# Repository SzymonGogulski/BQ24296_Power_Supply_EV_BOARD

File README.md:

# BQ24296 Power Supply 5V @ 3A

### Linki
* [Simple way to use USB-C 5V@3A](https://forum.digikey.com/t/simple-way-to-use-usb-type-c-to-get-5v-at-up-to-3a-15w/7016)

### Notatki
* BQ24296
    * Sprawdź default input current limit,
    * Sprawdź czy wyjście VSYS jest regulowane na 5.0V,
    * Sprawdź co to NVDC power path management,

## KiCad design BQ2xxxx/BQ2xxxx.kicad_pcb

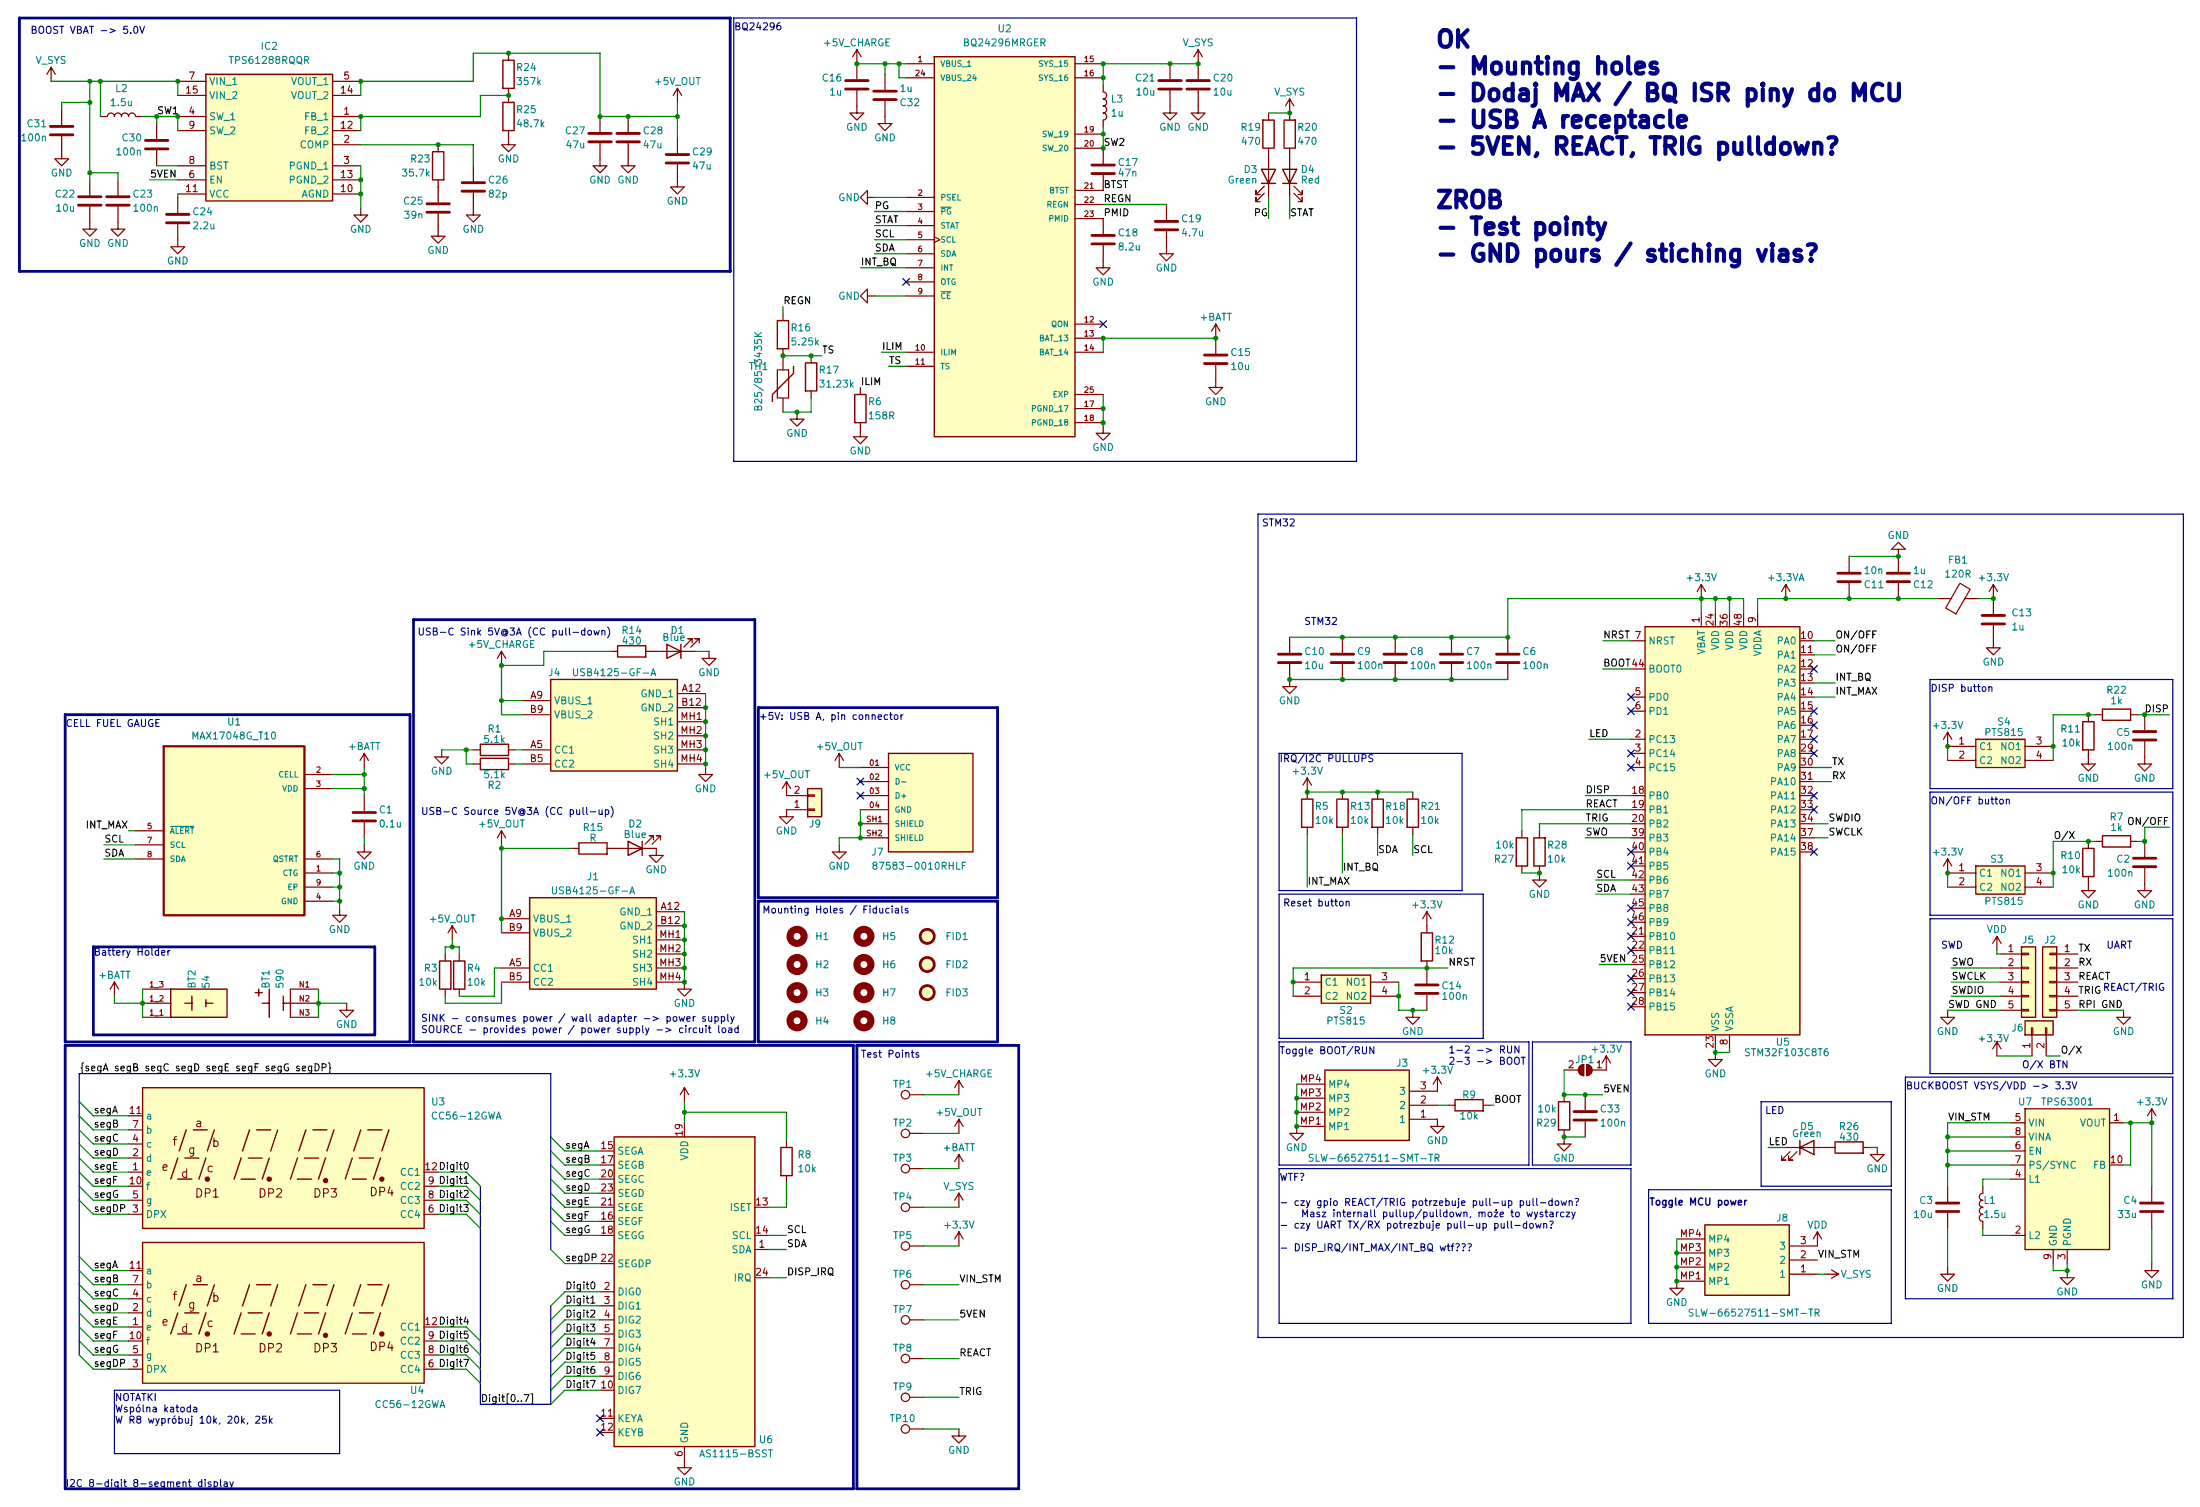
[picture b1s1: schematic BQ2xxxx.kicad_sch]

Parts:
BT1: 590; BAT_590; PARTREV E
BT2: 54; BAT_54; PARTREV E
C1: 0.1u; C_0402_1005Metric
C2, C5, C6, C7, C8, C9, C14, C23, C30, C31, C33: 100n; C_0402_1005Metric
C3, C10, C15, C20, C21: 10u; C_0603_1608Metric
C4: 33u; C_0805_2012Metric
C11: 10n; C_0402_1005Metric
C12, C13, C16, C32: 1u; C_0402_1005Metric
C17: 47n; C_0402_1005Metric
C18: 8.2u; C_0603_1608Metric
C19: 4.7u; C_0603_1608Metric
C22: 10u; C_0805_2012Metric
C24: 2.2u; C_0402_1005Metric
C25: 39n; C_0402_1005Metric
C26: 82p; C_0402_1005Metric
C27, C28, C29: 47u; C_0805_2012Metric
D1, D2: Blue; LED_0402_1005Metric
D3, D5: Green; LED_0402_1005Metric
D4: Red; LED_0402_1005Metric
FB1: 120R; R_0402_1005Metric
FID1, FID2, FID3: Fiducial; stencil_pin
H1, H2, H3, H4, H5, H6, H7, H8: MountingHole; MountingHole_2.2mm_M2
IC2: TPS61288RQQR; Mouser Part Number 595-TPS61288RQQR
J1, J4: USB4125-GF-A; USB4125GFA; Manufacturer_Part_Number USB4125-GF-A
J2, J5: Conn_01x05; PinSocket_1x05_P2.54mm_Vertical
J3, J8: SLW-66527511-SMT-TR; SLW66527511SMTTR; Mouser Part Number 179-SLW66527511SMTTR
J6, J9: Conn_01x02; PinHeader_1x02_P2.54mm_Vertical
J7: 87583-0010RHLF; AMPHENOL_87583-0010RHLF; PARTREV AD
JP1: SolderJumper_2_Open; R_0805_2012Metric
L1: 1.5u; L_1008_2520Metric
L2: 1.5u; L_6.3x6.3_H3
L3: 1u; IND_R2M01_VIS
R1, R2: 5.1k; R_0402_1005Metric
R3, R4, R5, R8, R9, R10, R11, R12, R13, R18, R21, R27, R28, R29: 10k; R_0402_1005Metric
R6: 158R; R_0402_1005Metric
R7, R22: 1k; R_0402_1005Metric
R14, R26: 430; R_0402_1005Metric
R15: R; R_0402_1005Metric
R16: 5.25k; R_0402_1005Metric
R17: 31.23k; R_0402_1005Metric
R19, R20: 470; R_0402_1005Metric
R23: 35.7k; R_0402_1005Metric
R24: 357k; R_0402_1005Metric
R25: 48.7k; R_0402_1005Metric
S2, S3, S4: PTS815; PTS815SJM250SMTRLFS; Mouser Part Number 611-PTS815SJM250SMTR
TH1: B25/85 3435K; R_0805_2012Metric
TP1, TP2, TP3, TP4, TP5, TP6, TP7, TP8, TP9: TestPoint; TestPoint_Pad_1.0x1.0mm
TP10: TestPoint; TestPoint_Pad_D3.0mm
U1: MAX17048G_T10; SON50P200X200X80-9N; DigiKey_Part_Number MAX17048G+T10TR-ND
U2: BQ24296MRGER; QFN50P400X400X100-25N; PARTREV 4219013/A 05/2017
U3, U4: CC56-12GWA
U5: STM32F103C8T6; LQFP-48_7x7mm_P0.5mm
U6: AS1115-BSST; QSOP-24_3.9x8.7mm_P0.635mm
U7: TPS63001; Texas_DRC0010J

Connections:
+3.3V: C4.1, C6.1, C7.1, C8.1, C9.1, C10.1, C13.1, FB1.2, J3.3, J6.1, JP1.1 (A), R5.1, R8.1, R12.1, R13.1, R18.1, R21.1, S3.1 (C1), S3.2 (C2), S4.1 (C1), S4.2 (C2), TP5.1, U5.1 (VBAT), U5.24 (VDD), U5.36 (VDD), U5.48 (VDD), U6.19 (VDD), U7.1 (VOUT), U7.10 (FB)
+3.3VA: C11.1, C12.1, FB1.1, U5.9 (VDDA)
+5V_CHARGE: C16.1, C32.2, J4.A9 (VBUS_1), J4.B9 (VBUS_2), R14.1, TP1.1, U2.1 (VBUS_1), U2.24 (VBUS_24)
+5V_OUT: C27.1, C28.1, C29.1, IC2.5 (VOUT_1), IC2.14 (VOUT_2), J1.A9 (VBUS_1), J1.B9 (VBUS_2), J7.01 (VCC), J9.2, R3.1, R4.1, R15.1, R24.1, TP2.1
+BATT: BT2.1_1, BT2.1_2, BT2.1_3, C1.1, C15.1, TP3.1, U1.2 (CELL), U1.3 (VDD), U2.13 (BAT_13), U2.14 (BAT_14)
/5VEN: C33.1, IC2.6 (EN), JP1.2 (B), R29.1, TP7.1, U5.25 (PB12)
/BOOT: R9.2, U5.44 (BOOT0)
/BTST: C17.2, U2.21 (BTST)
/DISP: C5.1, R22.2, U5.18 (PB0)
/DISP_IRQ: U6.24 (IRQ)
/Digit0: U3.12 (CC1), U6.2 (DIG0)
/Digit1: U3.9 (CC2), U6.3 (DIG1)
/Digit2: U3.8 (CC3), U6.4 (DIG2)
/Digit3: U3.6 (CC4), U6.5 (DIG3)
/Digit4: U4.12 (CC1), U6.7 (DIG4)
/Digit5: U4.9 (CC2), U6.8 (DIG5)
/Digit6: U4.8 (CC3), U6.9 (DIG6)
/Digit7: U4.6 (CC4), U6.10 (DIG7)
/ILIM: R6.1, U2.10 (ILIM)
/INT_BQ: R13.2, U2.7 (INT), U5.13 (PA3)
/INT_MAX: R5.2, U1.5 (~ALERT), U5.14 (PA4)
/LED: D5.1 (K), U5.2 (PC13)
/NRST: C14.1, R12.2, S2.1 (C1), S2.2 (C2), U5.7 (NRST)
/ON/OFF: C2.1, R7.2, U5.10 (PA0), U5.11 (PA1)
/O/X: J6.2, R7.1, R10.1, S3.3 (NO1), S3.4 (NO2)
/PG: D3.1 (K), U2.3 (~PG)
/PMID: C18.1, U2.23 (PMID)
/REACT: J2.3, R27.1, TP8.1, U5.19 (PB1)
/REGN: C19.1, R16.1, U2.22 (REGN)
/RX: J2.2, U5.31 (PA10)
/SCL: R21.2, U1.7 (SCL), U2.5 (SCL), U5.42 (PB6), U6.14 (SCL)
/SDA: R18.2, U1.8 (SDA), U2.6 (SDA), U5.43 (PB7), U6.1 (SDA)
/STAT: D4.1 (K), U2.4 (STAT)
/SW1: C30.2, IC2.4 (SW_1), IC2.9 (SW_2), L2.1
/SW2: C17.1, L3.2, U2.19 (SW_19), U2.20 (SW_20)
/SWCLK: J5.3, U5.37 (PA14)
/SWDIO: J5.4, U5.34 (PA13)
/SWO: J5.2, U5.39 (PB3)
/TRIG: J2.4, R28.2, TP9.1, U5.20 (PB2)
/TS: R16.2, R17.1, TH1.1, U2.11 (TS)
/TX: J2.1, U5.30 (PA9)
/VIN_STM: C3.1, J8.2, TP6.1, U7.5 (VIN), U7.6 (EN), U7.7 (PS/SYNC), U7.8 (VINA)
/segA: U3.11 (a), U4.11 (a), U6.15 (SEGA)
/segB: U3.7 (b), U4.7 (b), U6.17 (SEGB)
/segC: U3.4 (c), U4.4 (c), U6.20 (SEGC)
/segD: U3.2 (d), U4.2 (d), U6.23 (SEGD)
/segDP: U3.3 (DPX), U4.3 (DPX), U6.22 (SEGDP)
/segE: U3.1 (e), U4.1 (e), U6.21 (SEGE)
/segF: U3.10 (f), U4.10 (f), U6.16 (SEGF)
/segG: U3.5 (g), U4.5 (g), U6.18 (SEGG)
GND: BT1.N1, BT1.N2, BT1.N3, C1.2, C2.2, C3.2, C4.2, C5.2, C6.2, C7.2, C8.2, C9.2, C10.2, C11.2, C12.2, C13.2, C14.2, C15.2, C16.2, C18.2, C19.2, C20.2, C21.2, C22.1, C23.2, C24.2, C25.2, C26.2, C27.2, C28.2, C29.2, C31.2, C32.1, C33.2, D1.1 (K), D2.1 (K), IC2.3 (PGND_1), IC2.10 (AGND), IC2.13 (PGND_2), J1.A12 (GND_1), J1.B12 (GND_2), J1.MH1 (SH1), J1.MH2 (SH2), J1.MH3 (SH3), J1.MH4 (SH4), J2.5, J3.1, J3.MP1, J3.MP2, J3.MP3, J3.MP4, J4.A12 (GND_1), J4.B12 (GND_2), J4.MH1 (SH1), J4.MH2 (SH2), J4.MH3 (SH3), J4.MH4 (SH4), J5.5, J7.04 (GND), J7.SH1 (SHIELD), J7.SH2 (SHIELD), J8.MP1, J8.MP2, J8.MP3, J8.MP4, J9.1, R1.1, R2.1, R6.2, R10.2, R11.2, R17.2, R25.2, R26.2, R27.2, R28.1, R29.2, S2.3 (NO1), S2.4 (NO2), TH1.2, TP10.1, U1.1 (CTG), U1.4 (GND), U1.6 (QSTRT), U1.9 (EP), U2.2 (PSEL), U2.9 (~CE), U2.17 (PGND_17), U2.18 (PGND_18), U2.25 (EXP), U5.8 (VSSA), U5.23 (VSS), U5.35 (VSS), U5.47 (VSS), U6.6 (GND), U7.3 (PGND), U7.9 (GND), U7.11 (PGND)
unnamed: C25.1, R23.2
unnamed: D1.2 (A), R14.2
unnamed: D2.2 (A), R15.2
unnamed: D3.2 (A), R19.1
unnamed: D4.2 (A), R20.1
unnamed: D5.2 (A), R26.1
unnamed: C30.1, IC2.8 (BST)
unnamed: C26.1, IC2.2 (COMP), R23.1
unnamed: IC2.1 (FB_1), IC2.12 (FB_2), R24.2, R25.1
unnamed: C24.1, IC2.11 (VCC)
unnamed: J1.A5 (CC1), R4.2
unnamed: J1.B5 (CC2), R3.2
unnamed: J3.2, R9.1
unnamed: J4.A5 (CC1), R1.2
unnamed: J4.B5 (CC2), R2.2
unnamed: R11.1, R22.1, S4.3 (NO1), S4.4 (NO2)
unnamed: R8.2, U6.13 (ISET)
unnamed: L1.2, U7.4 (L1)
unnamed: L1.1, U7.2 (L2)
VDD: J5.1, J8.3
V_SYS: C20.1, C21.1, C22.2, C23.1, C31.1, IC2.7 (VIN_1), IC2.15 (VIN_2), J8.1, L2.2, L3.1, R19.2, R20.2, TP4.1, U2.15 (SYS_15), U2.16 (SYS_16)

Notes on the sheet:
Reset button
USB-C Source 5V@3A (CC pull-up)
Battery Holder
Mounting Holes / Fiducials
BUCKBOOST VSYS/VDD -> 3.3V
ON/OFF button
IRQ/I2C PULLUPS
DISP button
UART
STM32
LED
O/X BTN
WTF?
REACT/TRIG
SINK - consumes power / wall adapter -> power supply SOURCE - provides power / power supply -> circuit load
USB-C Sink 5V@3A (CC pull-down)
Toggle BOOT/RUN
Test Points
- czy gpio REACT/TRIG potrzebuje pull-up pull-down? Masz internall pullup/pulldown, może to wystarczy - czy UART TX/RX potrezbuje pull-up pull-down? - DISP_IRQ/INT_MAX/INT_BQ wtf???
1-2 -> RUN 2-3 -> BOOT
NOTATKI Wspólna katoda W R8 wypróbuj 10k, 20k, 25k
CELL FUEL GAUGE
BQ24296
SWD
BOOST VBAT -> 5.0V
+5V: USB A, pin connector
I2C 8-digit 8-segment display
OK - Mounting holes - Dodaj MAX / BQ ISR piny do MCU - USB A receptacle - 5VEN, REACT, TRIG pulldown? ZROB - Test pointy - GND pours / stiching vias?
Toggle MCU power

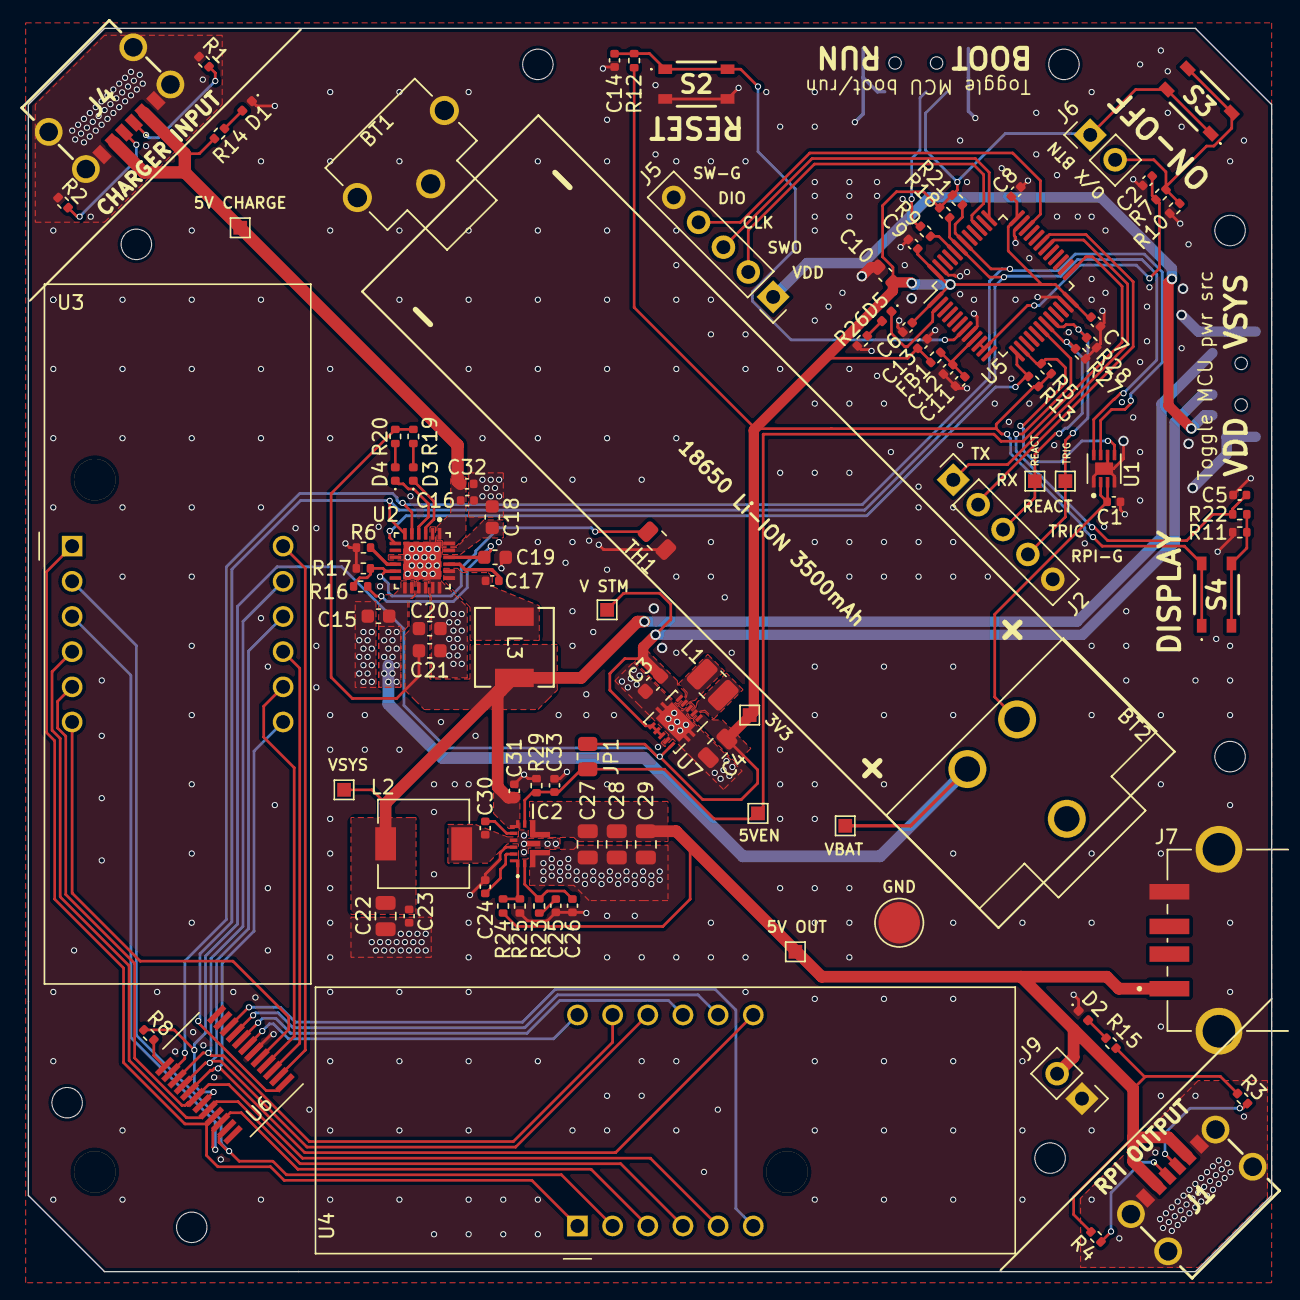
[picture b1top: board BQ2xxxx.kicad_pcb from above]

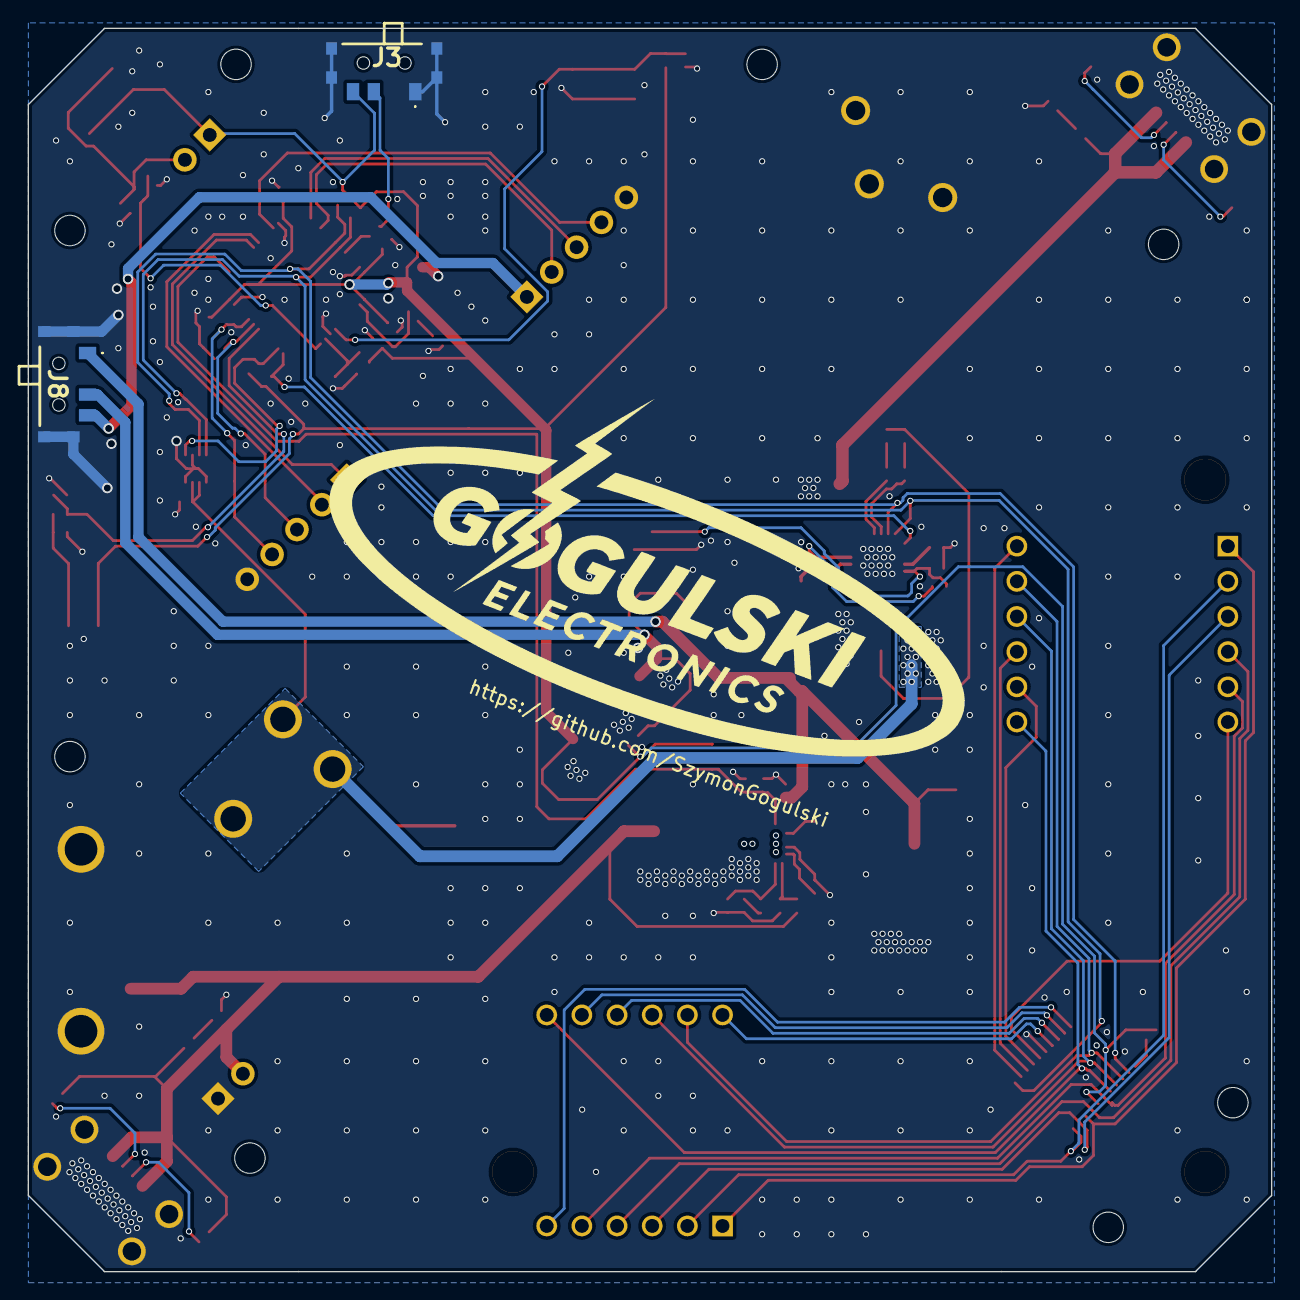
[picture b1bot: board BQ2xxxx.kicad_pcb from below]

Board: 4 copper layers, 89.8 x 89.8 mm, 116 parts (2 on the bottom side), 71 nets.

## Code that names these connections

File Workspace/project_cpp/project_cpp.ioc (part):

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Mcu.Name=STM32F411C(C-E)Ux
Mcu.Package=UFQFPN48
Mcu.UserName=STM32F411CEUx
PA0-WKUP.GPIOParameters=GPIO_Label
PA0-WKUP.GPIO_Label=ON
PA0-WKUP.Mode=SYS_WakeUp0
PA0-WKUP.Signal=SYS_WKUP
PA1.GPIOParameters=GPIO_Label
PA1.GPIO_Label=OFF
PA1.Signal=GPIO_Input
PA10.Mode=Asynchronous
PA10.Signal=USART1_RX
PA13.Mode=Trace_Asynchronous_SW
PA13.Signal=SYS_JTMS-SWDIO
PA14.Mode=Trace_Asynchronous_SW
PA14.Signal=SYS_JTCK-SWCLK
PA3.GPIOParameters=GPIO_Label
PA3.GPIO_Label=INT_BQ
PA3.Signal=GPIO_Input
PA4.GPIOParameters=GPIO_Label
PA4.GPIO_Label=INT_MAX
PA4.Signal=GPIO_Input
PA9.Mode=Asynchronous
PA9.Signal=USART1_TX
PB0.GPIOParameters=GPIO_Label
PB0.GPIO_Label=DISP
PB0.Signal=GPIO_Input
PB1.GPIOParameters=GPIO_Label
PB1.GPIO_Label=REACT
PB1.Signal=GPIO_Input
PB12.GPIOParameters=GPIO_Label
PB12.GPIO_Label=EN5V
PB12.Signal=GPIO_Output
PB2.GPIOParameters=GPIO_Label
PB2.GPIO_Label=TRIG
PB2.Signal=GPIO_Output
PB3.Mode=Trace_Asynchronous_SW
PB3.Signal=SYS_JTDO-SWO
PB6.Mode=I2C
PB6.Signal=I2C1_SCL
PB7.Mode=I2C
PB7.Signal=I2C1_SDA
PB9.Signal=GPIO_Output
PC13-ANTI_TAMP.GPIOParameters=GPIO_Label
PC13-ANTI_TAMP.GPIO_Label=LED
PC13-ANTI_TAMP.Signal=GPIO_Output
RCC.HSE_VALUE=25000000
RCC.SYSCLKFreq_VALUE=16000000
board=custom

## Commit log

2025-06-23 INIT
2025-06-25 MAIN: 25.06.2025
2025-07-10 Work in progress: Schematic
2025-08-14 14.08 save
2025-08-27 PCB wersja 1.0 koniec
